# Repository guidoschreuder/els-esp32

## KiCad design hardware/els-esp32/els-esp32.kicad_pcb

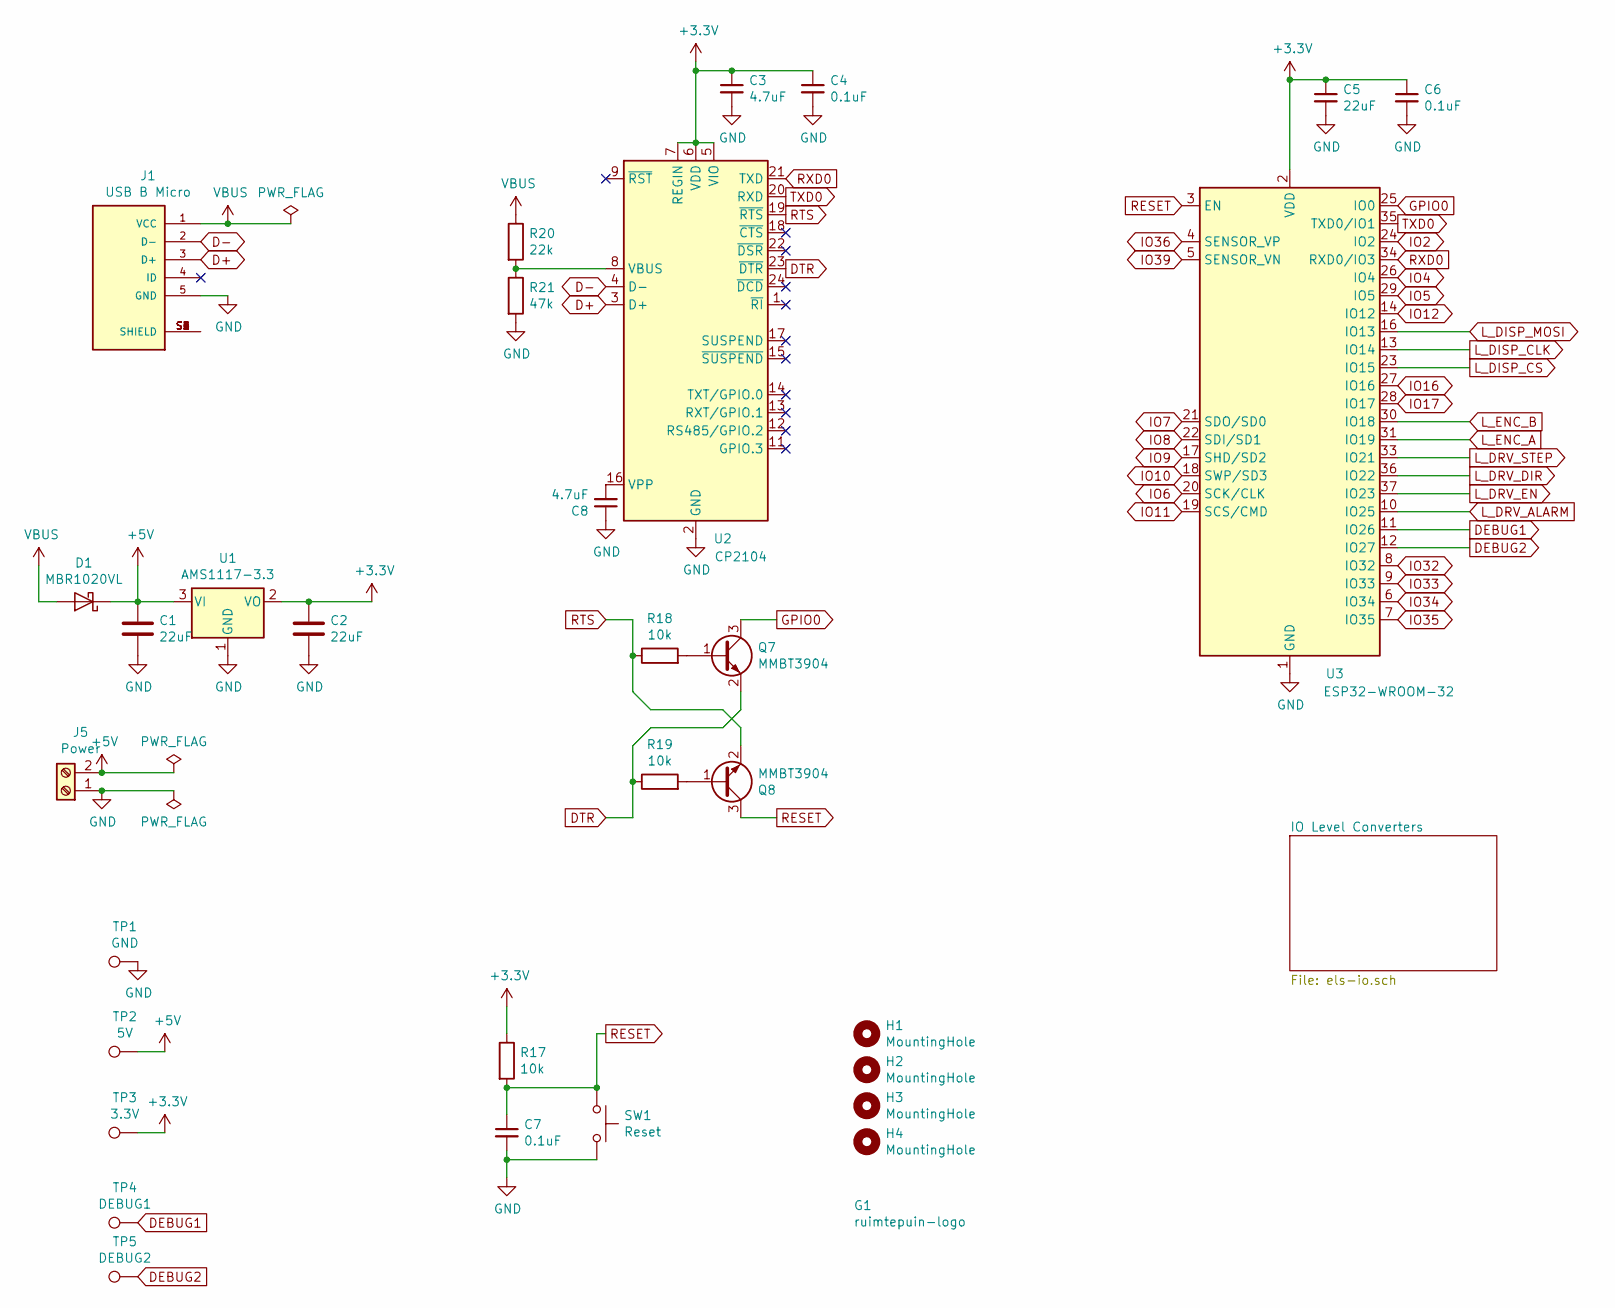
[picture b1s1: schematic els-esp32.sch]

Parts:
C1, C2, C5: 22uF; C_0603_1608Metric; LCSC C59461
C3, C8: 4.7uF; C_0402_1005Metric; LCSC C23733
C4, C6, C7: 0.1uF; C_0402_1005Metric; LCSC C1525
D1: MBR1020VL; D_SOD-123F
G1: ruimtepuin-logo
H1, H2, H3, H4: MountingHole; MountingHole_3mm_Pad_TopBottom
J1: USB B Micro; AMPHENOL_10118192-0002LF; PARTREV B
J5: Power; TerminalBlock_4Ucon_1x02_P3.50mm_Horizontal
Q7, Q8: MMBT3904; SOT-23; LCSC C20526
R17, R18, R19: 10k; R_0603_1608Metric; LCSC C25804
R20: 22k; R_0603_1608Metric; LCSC C25804
R21: 47k; R_0603_1608Metric; LCSC C25804
SW1: Reset; SW_SPST_EVQPE1
TP1: GND; TestPoint_THTPad_D1.5mm_Drill0.7mm
TP2: 5V; TestPoint_THTPad_D1.5mm_Drill0.7mm
TP3: 3.3V; TestPoint_THTPad_D1.5mm_Drill0.7mm
TP4: DEBUG1; TestPoint_THTPad_D1.5mm_Drill0.7mm
TP5: DEBUG2; TestPoint_THTPad_D1.5mm_Drill0.7mm
U1: AMS1117-3.3; SOT-223-3_TabPin2; LCSC C6186
U2: CP2104; QFN-24-1EP_4x4mm_P0.5mm_EP2.6x2.6mm
U3: ESP32-WROOM-32

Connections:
+3V3: C2.1, C3.1, C4.1, C5.1, C6.1, R17.1, TP3.1, U1.2 (VO), U2.5 (VIO), U2.6 (VDD), U2.7 (REGIN), U3.2 (VDD); also elsewhere on the board
+5V: C1.1, D1.1 (K), J5.2, TP2.1, U1.3 (VI); also elsewhere on the board
D+: J1.3 (D+), U2.3 (D+)
D-: J1.2 (D-), U2.4 (D-)
DEBUG1: TP4.1, U3.11 (IO26)
DEBUG2: TP5.1, U3.12 (IO27)
DTR: Q7.2 (E), R19.1, U2.23 (~DTR)
GND: C1.2, C2.2, C3.2, C4.2, C5.2, C6.2, C7.2, C8.1, J1.5 (GND), J5.1, R21.2, SW1.2, TP1.1, U1.1 (GND), U2.2 (GND), U2.25 (GND), U3.1 (GND), U3.15 (GND), U3.38 (GND), U3.39 (GND); also elsewhere on the board
GPIO0: Q7.3 (C), U3.25 (IO0)
IO2: U3.24 (IO2); also elsewhere on the board
IO4: U3.26 (IO4); also elsewhere on the board
IO5: U3.29 (IO5); also elsewhere on the board
IO6: U3.20 (SCK/CLK); also elsewhere on the board
IO7: U3.21 (SDO/SD0); also elsewhere on the board
IO8: U3.22 (SDI/SD1); also elsewhere on the board
IO9: U3.17 (SHD/SD2); also elsewhere on the board
IO10: U3.18 (SWP/SD3); also elsewhere on the board
IO11: U3.19 (SCS/CMD); also elsewhere on the board
IO12: U3.14 (IO12); also elsewhere on the board
IO16: U3.27 (IO16); also elsewhere on the board
IO17: U3.28 (IO17); also elsewhere on the board
IO32: U3.8 (IO32); also elsewhere on the board
IO33: U3.9 (IO33); also elsewhere on the board
IO34: U3.6 (IO34); also elsewhere on the board
IO35: U3.7 (IO35); also elsewhere on the board
IO36: U3.4 (SENSOR_VP); also elsewhere on the board
IO39: U3.5 (SENSOR_VN); also elsewhere on the board
L_DISP_CLK: U3.13 (IO14); also elsewhere on the board
L_DISP_CS: U3.23 (IO15); also elsewhere on the board
L_DISP_MOSI: U3.16 (IO13); also elsewhere on the board
L_DRV_ALARM: U3.10 (IO25); also elsewhere on the board
L_DRV_DIR: U3.36 (IO22); also elsewhere on the board
L_DRV_EN: U3.37 (IO23); also elsewhere on the board
L_DRV_STEP: U3.33 (IO21); also elsewhere on the board
L_ENC_A: U3.31 (IO19); also elsewhere on the board
L_ENC_B: U3.30 (IO18); also elsewhere on the board
unnamed: C8.2, U2.16 (VPP)
unnamed: J1.S1 (SHIELD), J1.S2 (SHIELD), J1.S3 (SHIELD), J1.S4 (SHIELD), J1.S5 (SHIELD), J1.S6 (SHIELD)
unnamed: Q7.1 (B), R18.2
unnamed: Q8.1 (B), R19.2
unnamed: R20.2, R21.1, U2.8 (VBUS)
RESET: C7.1, Q8.3 (C), R17.2, SW1.1, U3.3 (EN)
RTS: Q8.2 (E), R18.1, U2.19 (~RTS)
RXD0: U2.21 (TXD), U3.34 (RXD0/IO3)
TXD0: U2.20 (RXD), U3.35 (TXD0/IO1)
VBUS: D1.2 (A), J1.1 (VCC), R20.1

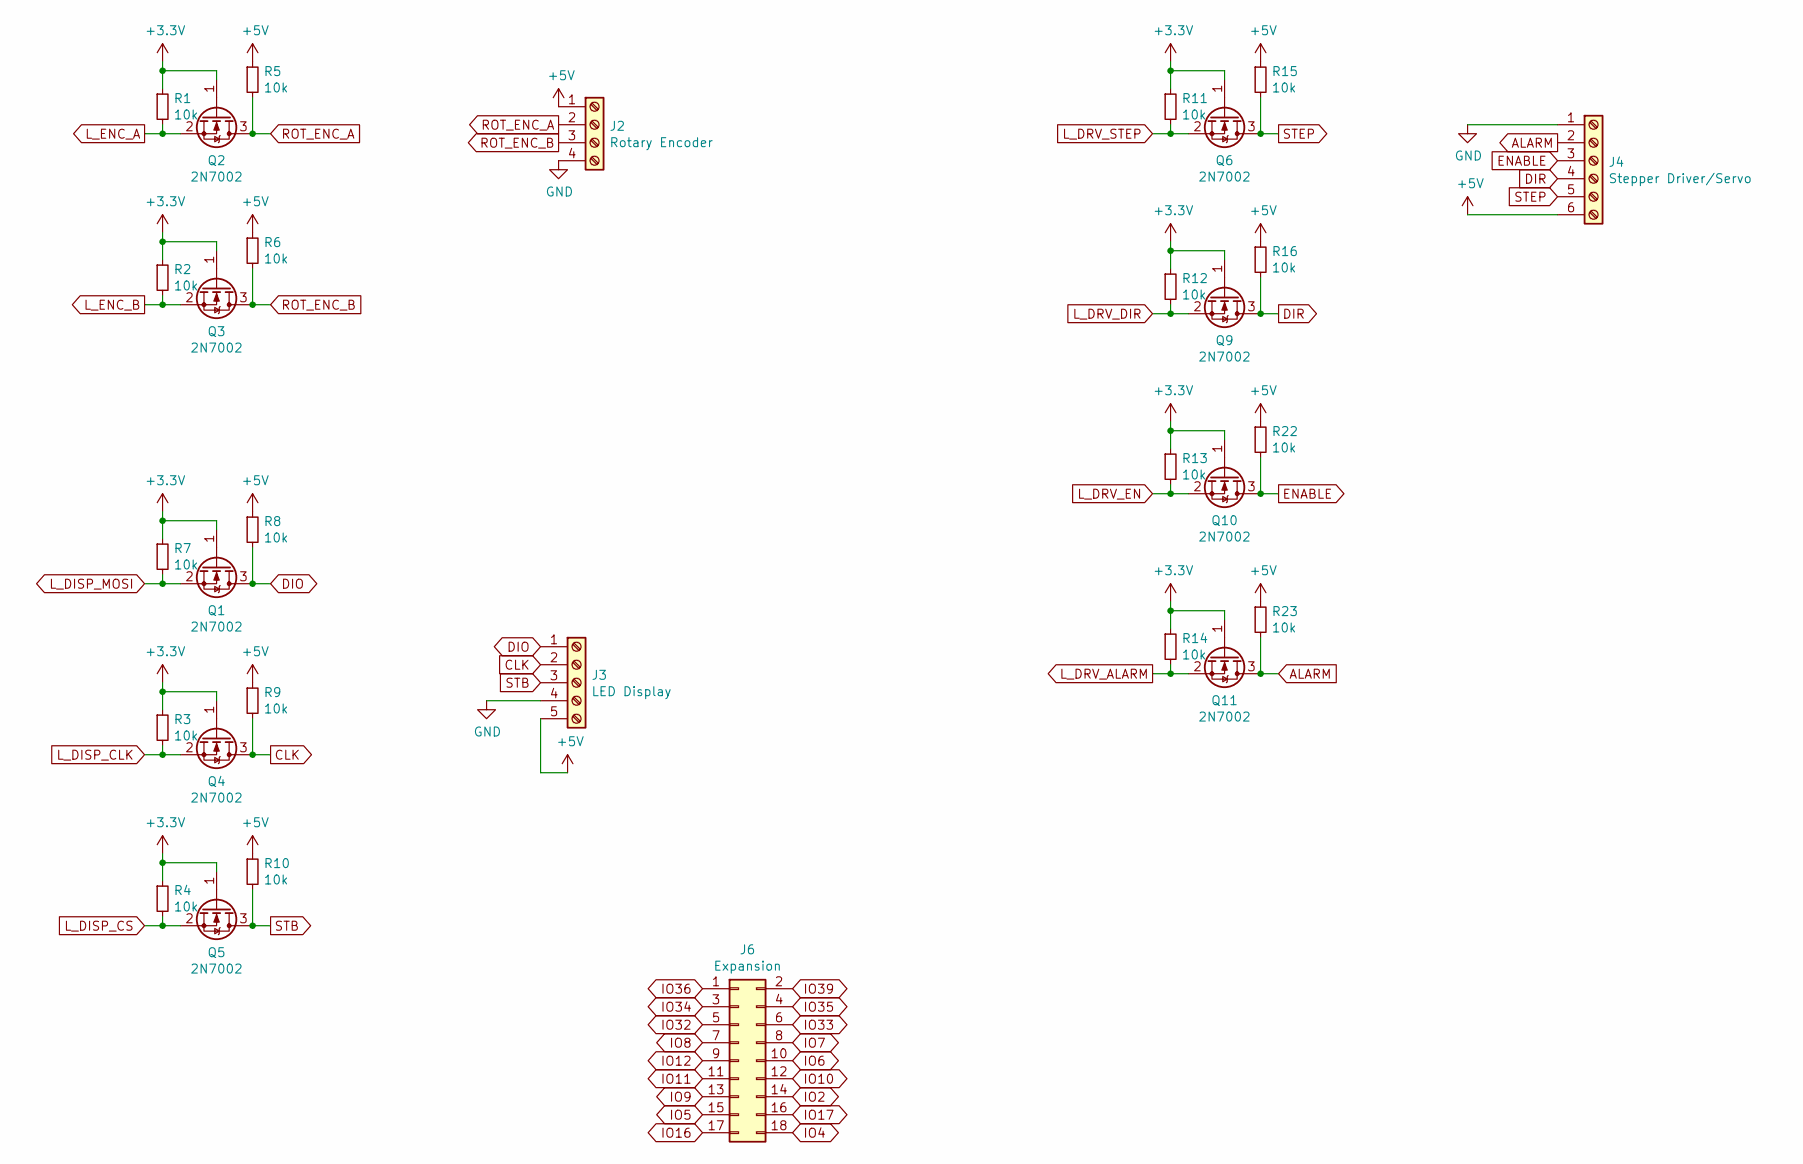
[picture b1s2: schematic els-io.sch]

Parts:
J2: Rotary Encoder; TerminalBlock_4Ucon_1x04_P3.50mm_Horizontal
J3: LED Display; PinHeader_1x05_P2.54mm_Vertical
J4: Stepper Driver/Servo; TerminalBlock_4Ucon_1x06_P3.50mm_Horizontal
J6: Expansion; PinHeader_2x09_P2.54mm_Vertical
Q1, Q2, Q3, Q4, Q5, Q6, Q9, Q10, Q11: 2N7002; SOT-23; LCSC C8545
R1, R2, R3, R4, R5, R6, R7, R8, R9, R10, R11, R12, R13, R14, R15, R16, R22, R23: 10k; R_0603_1608Metric; LCSC C25804

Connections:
+3V3: Q1.1 (G), Q2.1 (G), Q3.1 (G), Q4.1 (G), Q5.1 (G), Q6.1 (G), Q9.1 (G), Q10.1 (G), Q11.1 (G), R1.1, R2.1, R3.1, R4.1, R7.1, R11.1, R12.1, R13.1, R14.1; also elsewhere on the board
+5V: J2.1, J3.5, J4.6, R5.1, R6.1, R8.1, R9.1, R10.1, R15.1, R16.1, R22.1, R23.1; also elsewhere on the board
ALARM: J4.2, Q11.3 (D), R23.2
CLK: J3.2, Q4.3 (D), R9.2
DIO: J3.1, Q1.3 (D), R8.2
DIR: J4.4, Q9.3 (D), R16.2
ENABLE: J4.3, Q10.3 (D), R22.2
GND: J2.4, J3.4, J4.1; also elsewhere on the board
IO2: J6.14; also elsewhere on the board
IO4: J6.18; also elsewhere on the board
IO5: J6.15; also elsewhere on the board
IO6: J6.10; also elsewhere on the board
IO7: J6.8; also elsewhere on the board
IO8: J6.7; also elsewhere on the board
IO9: J6.13; also elsewhere on the board
IO10: J6.12; also elsewhere on the board
IO11: J6.11; also elsewhere on the board
IO12: J6.9; also elsewhere on the board
IO16: J6.17; also elsewhere on the board
IO17: J6.16; also elsewhere on the board
IO32: J6.5; also elsewhere on the board
IO33: J6.6; also elsewhere on the board
IO34: J6.3; also elsewhere on the board
IO35: J6.4; also elsewhere on the board
IO36: J6.1; also elsewhere on the board
IO39: J6.2; also elsewhere on the board
L_DISP_CLK: Q4.2 (S), R3.2; also elsewhere on the board
L_DISP_CS: Q5.2 (S), R4.2; also elsewhere on the board
L_DISP_MOSI: Q1.2 (S), R7.2; also elsewhere on the board
L_DRV_ALARM: Q11.2 (S), R14.2; also elsewhere on the board
L_DRV_DIR: Q9.2 (S), R12.2; also elsewhere on the board
L_DRV_EN: Q10.2 (S), R13.2; also elsewhere on the board
L_DRV_STEP: Q6.2 (S), R11.2; also elsewhere on the board
L_ENC_A: Q2.2 (S), R1.2; also elsewhere on the board
L_ENC_B: Q3.2 (S), R2.2; also elsewhere on the board
ROT_ENC_A: J2.2, Q2.3 (D), R5.2
ROT_ENC_B: J2.3, Q3.3 (D), R6.2
STB: J3.3, Q5.3 (D), R10.2
STEP: J4.5, Q6.3 (D), R15.2

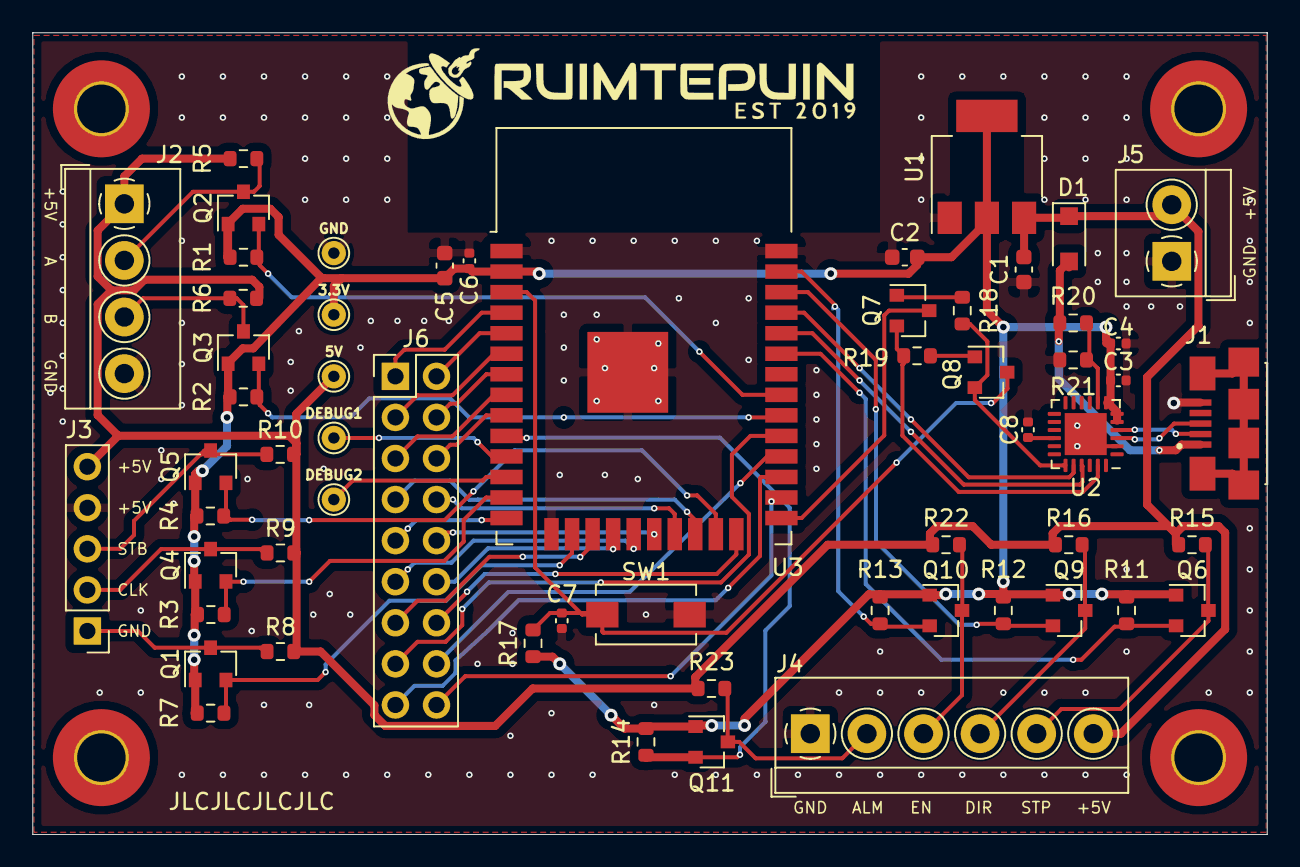
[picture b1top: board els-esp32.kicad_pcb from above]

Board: 2 copper layers, 76.3 x 49.6 mm, 63 parts (0 on the bottom side), 55 nets.

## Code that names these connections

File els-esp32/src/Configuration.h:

// Clough42 Electronic Leadscrew
// https://github.com/clough42/electronic-leadscrew
//
// MIT License
//
// Copyright (c) 2019 James Clough
//
// Permission is hereby granted, free of charge, to any person obtaining a copy
// of this software and associated documentation files (the "Software"), to deal
// in the Software without restriction, including without limitation the rights
// to use, copy, modify, merge, publish, distribute, sublicense, and/or sell
// copies of the Software, and to permit persons to whom the Software is
// furnished to do so, subject to the following conditions:
//
// The above copyright notice and this permission notice shall be included in all
// copies or substantial portions of the Software.
//
// THE SOFTWARE IS PROVIDED "AS IS", WITHOUT WARRANTY OF ANY KIND, EXPRESS OR
// IMPLIED, INCLUDING BUT NOT LIMITED TO THE WARRANTIES OF MERCHANTABILITY,
// FITNESS FOR A PARTICULAR PURPOSE AND NONINFRINGEMENT. IN NO EVENT SHALL THE
// AUTHORS OR COPYRIGHT HOLDERS BE LIABLE FOR ANY CLAIM, DAMAGES OR OTHER
// LIABILITY, WHETHER IN AN ACTION OF CONTRACT, TORT OR OTHERWISE, ARISING FROM,
// OUT OF OR IN CONNECTION WITH THE SOFTWARE OR THE USE OR OTHER DEALINGS IN THE
// SOFTWARE.


#ifndef __CONFIGURATION_H
#define __CONFIGURATION_H


#define DISP_SPI_HOST    HSPI_HOST

//================================================================================
//                                  PINS
// debug pins
#define DEBUG1_GPIO     26
#define DEBUG2_GPIO     27

// encoder pins
#define ENCODER_A_GPIO  19
#define ENCODER_B_GPIO  18

// stepper pins
#define STEP_GPIO       21
#define DIRECTION_GPIO  22
#define ENABLE_GPIO     23
#define ALARM_GPIO      25

// control panel pins
#define DISP_MOSI_GPIO  13
#define DISP_CLK_GPIO   14
#define DISP_CS_GPIO    15



//================================================================================
//                                  LEADSCREW
//
// Define the type and pitch of leadscrew you have in your lathe.  If you have an
// imperial leadscrew, define LEADSCREW_TPI.  If you have a metric leadscrew,
// define LEADSCREW_HMM (pitch in hundredths of a millimeter).  Do not define
// both.
//================================================================================

// For Imperial leadscrews: pitch in Threads Per Inch (TPI)
#define LEADSCREW_TPI 12

// For metric leadscrews: pitch in hundredths of a millimeter (HMM)
// Example: 200hmm = 2mm
//#define LEADSCREW_HMM 200




//================================================================================
//                                STEPPER/SERVO
//
// Define the number of steps and microsteps for your stepper motor, the pin
// polarity of the driver, and whether to use additional features, like servo
// alarm feedback.
//
// NOTE: If you are using a servo drive with something other than a 1:1 drive
// ratio, you can use the STEPPER_MICROSTEPS to compensate.  For example, if you
// have a servo configured for 1000 steps/revolution and it drives the leadscrew
// through a 3:1 reduction, you can set STEPPER_RESOLUTION to 1000 and
// STEPPER_MICROSTEPS to 3.
//================================================================================

// Steps and microsteps
#define STEPPER_MICROSTEPS 8
#define STEPPER_RESOLUTION 200

// Separate step and microstep settings for feed rates.  Redefine these if your
// lathe has a separate feed drive train with a different ratio.
#define STEPPER_MICROSTEPS_FEED STEPPER_MICROSTEPS
#define STEPPER_RESOLUTION_FEED STEPPER_RESOLUTION

// Step, direction and enable pins are normally active-high
// #define INVERT_STEP_GPIO true
// #define INVERT_DIRECTION_GPIO true
#define INVERT_ENABLE_GPIO true
#define INVERT_ALARM_GPIO true

// Enable servo alarm feedback
#define USE_ALARM_GPIO

// Stepper RMT channel
#define STEPPER_RMT_CHANNEL RMT_CHANNEL_0



//================================================================================
//                                 ENCODER
//
// Define the type of encoder you are using on the spindle.  The firmware assumes
// the encoder is turning at a 1:1 ratio with the spindle.
//
// NOTE: the firmware is concerned with the quadrature edge count, which is
// four times the number of pulses.  For example, if you have a 1024 P/R
// encoder, you need to enter 4096 here.
//================================================================================

// Encoder resolution (counts per revolution)
#define ENCODER_RESOLUTION 4096

// Which encoder input to use
#define ENCODER_USE_EQEP1
//#define ENCODER_USE_EQEP2




//================================================================================
//                               CALCULATIONS
//
// Define how calculations should be performed.  Most users will not need to
// touch these settings.
//================================================================================

// Use floating-point math for gear ratios
//#define USE_FLOATING_POINT




//================================================================================
//                                HARDWARE
//
// Define which hardware you're using:
//
//  1 - LaunchXL F280049C with ELS BoostXL v1
//  2 - LaunchXL F280049C with ELS BoostXL v2
//================================================================================

// See hardware version table above
#define HARDWARE_VERSION 2




//================================================================================
//                                FEATURES
//
// Additional features that can be enabled for your configuration.
//================================================================================

// Ignore all key presses when the machine is running.  Normally, only the mode
// and direction keys are ignored.
//#define IGNORE_ALL_KEYS_WHEN_RUNNING




//================================================================================
//                              VALIDATION/TRIP
//
// Validation thresholds and automatic trip behavior.
//================================================================================

// Maximum number of buffered steps
// The ELS can only output steps at approximately 100KHz.  If you ask the ELS to
// output steps faster than this, it will get behind and will stop automatically
// when the buffered step count exceeds this value.
#define MAX_BUFFERED_STEPS 100


//================================================================================
//                               CPU / TIMING
//
// Define the CPU clock, interrupt, and refresh timing.  Most users will not need
// to touch these settings.
//================================================================================

// Core service CPU
#define CORE_SERVICE_CPU_CORE APP_CPU_NUM

// Frequency of main control loop
#define CONTROL_FREQ_HZ 20000

// Stepper state machine cycle time, in microseconds
// Two cycles are required per step
#define STEPPER_CYCLE_US 3

// User interface refresh rate, in Hertz
#define UI_REFRESH_RATE_HZ 100

// RPM recalculation rate, in Hz
#define RPM_CALC_RATE_HZ 2

#endif // __CONFIGURATION_H

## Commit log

2022-06-30 Port encoder-sim to platformio
2022-07-03 UNTESTED: ported most of the code, except SPI
2022-07-03 add .gitignore
2022-07-03 Add upload_port for encoder-sim
2022-07-05 Fix masks for gpio setup
2022-07-05 Use correct pin for debug2
2022-07-05 Enable pull-down for debug pins
2022-07-05 UNTESTED: First stab at controlling display, SPIBus.* files removed as it translated poorly to ESP32, ControlPanel.c directly uses SPI
2022-07-05 Display working
2022-07-05 Add platformio log files
2022-07-05 add .gitattributes file
2022-07-05 renormalize all source files
2022-07-05 Added comment about limitation of current timer setup
2022-07-05 remove obsolete code
2022-07-06 Set integer math as default
2022-07-06 Store all encoder positions as int64
2022-07-06 Move to espressif32@5.0.0 and pin the version in platformio.ini
2022-07-08 Add macro to cleanup leds definitions
2022-07-08 Remove unused CPU_CLOCK definitions
2022-07-09 Use hardware timer
2022-07-09 Fix potential overflow
2022-07-14 Reduce lower bounds on STEPPER_CYCLE_US and correct error message
2022-07-14 Use int64_t for all tables
2022-07-14 remove unused variable
2022-07-15 use RMT for driving step pin
2022-07-16 Use queue to send state changes to core
2022-07-16 Simplify logic in StepperDrive
2022-07-17 Use queueu of size one and overwrites for sending info from UI to Core
2022-07-17 Remove additional interrupt as it was not the cause of excessive backlog
2022-07-18 Add config option for core service CPU affinity
2022-07-20 Use ESP32Encoder through lib_deps
2022-07-20 Pin ISR service to same core as core-service
2022-07-20 Re-enable panic now that concurrency issue is resolved
2022-07-20 Declare enabled as volatile since it might be written by another thread/core
2022-07-21 Use initializer list for constructor, use getPosition() in getRpm()
2022-07-22 Point to main branch in modified ESP32Encoder library
2022-07-22 remove temporary debug code for concurrency issue
2022-07-23 dev commit: simplify debug
2022-07-23 Use initializer list for stepper constructor
2022-07-23 Messed up setting the state of the stepper
2022-07-23 minor clean: rename parameter
2022-07-24 remove commented out code
2022-07-24 Add TODO
2022-09-18 First version of board
2022-10-02 minor layout
2022-10-03 Fixed hardware bug, one transistor was reversed
2022-12-09 Add platformio section for ELS
